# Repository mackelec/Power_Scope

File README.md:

# Power_Scope
Power Scope for $10

https://www.thebackshed.com/forum/forum_posts.asp?TID=11123&PN=1

Software is still a work in progress.

A minimal Oscilloscope design utilising a STM32F103 "Blue Pill" and a cheap mcuFriend 2.4" LCD, specifically to display the output voltage for an Inverter.  Along with displaying th eAc waveform it will display RMS voltage, Current and Power.

LCD library is compatible with the 8bit mcuFriend 2.4" and 3.5" LCD.

PCD features:

PCB is compatible with the 8 bit mcuFriend "UNO" lcds as well as the SPI based LCDs.

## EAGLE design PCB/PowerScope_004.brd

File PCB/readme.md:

"PowerScope_004_PCB_Order_20190317.zip"  contains the files sent for PCB manufacture.

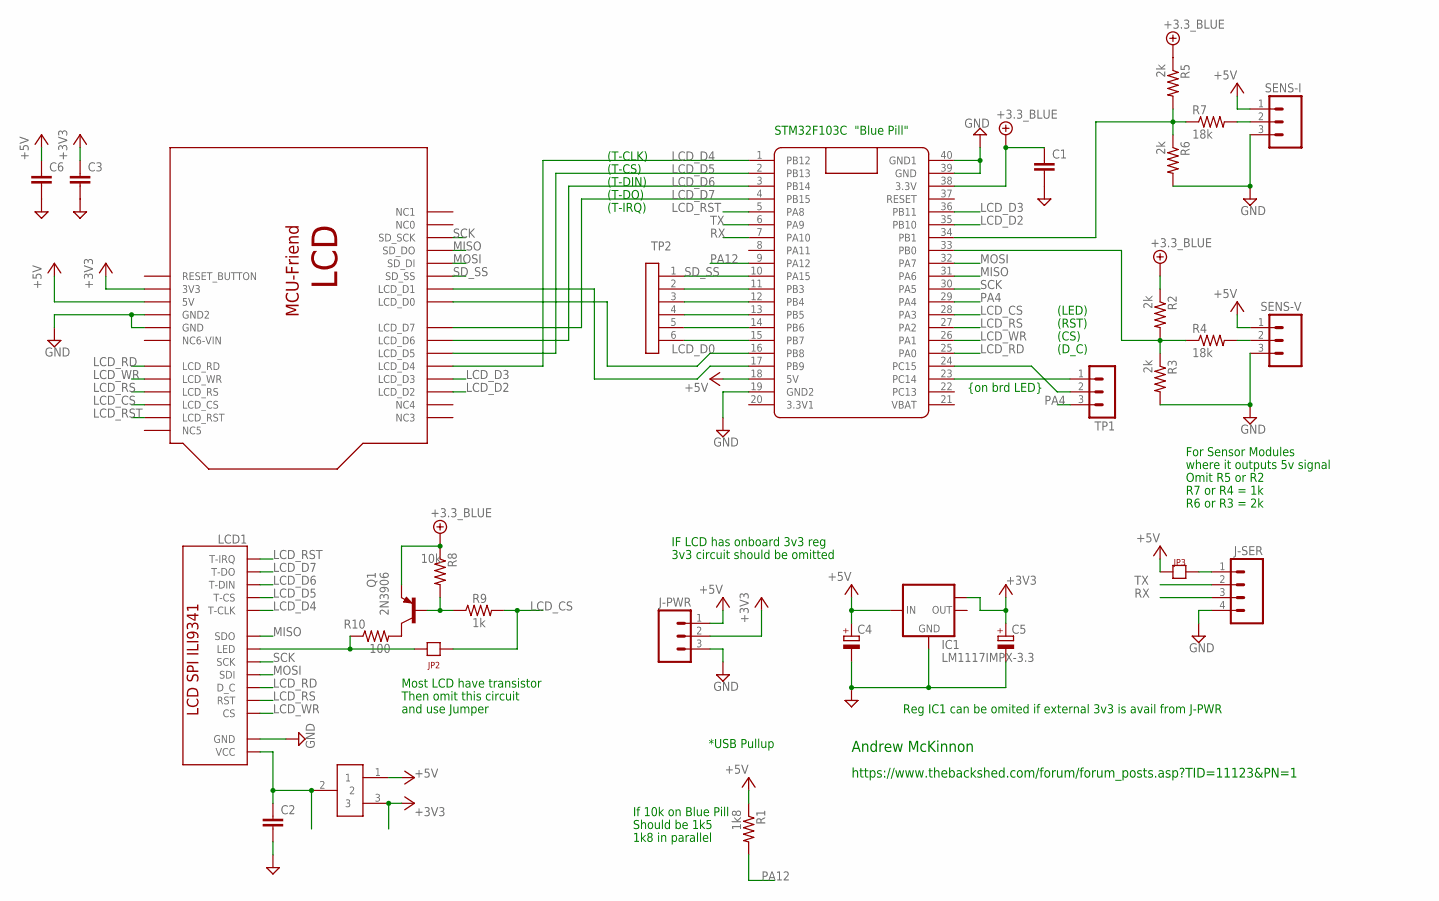
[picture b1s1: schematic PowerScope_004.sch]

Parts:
C1, C2, C3, C6: BCAP
C4, C5: C-RB200100; CPOL-RADIAL-10UF-25V
IC1: LM1117IMPX-3.3; SOT223
J-PWR: MO3POL; MOLEX-3
J-SER: MO4POL; MOLEX-4
JP1: JP1X3
JP2, JP3: JP1
LCD1: LCD_ILI9341_SPI_TREV; LCD_ILI9341_SPI_24T_REVERSE
Q1: 2N3906; TO92
R1: 1k8; R4_SP
R2, R3, R5, R6: 2k; R4_SP
R4, R7: 18k; R4_SP
R8: 10k; R4_SP
R9: 1k; R4_SP
R10: 100; R4_SP
SENS-I: MO3POL; MOLEX-3
SENS-V: MO3POL; MOLEX-3
TP1: MA03-1
TP2: SIL-6; SIL6
U$2: LCD_MCUFRIENDREV; LCD-MCUFRIEND-24T-REV
U$3: BLUE_PILL; BLUE_PILL_CLEAN

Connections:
+3V3: C3.1, C5.1 (+), IC1.TAB (OUT1), J-PWR.2, JP1.3, U$2.3V (3V3)
+5V: C4.1 (+), C6.1, IC1.3 (IN), J-PWR.1, JP1.1, JP3.1, R1.P$1 (1), SENS-I.1, SENS-V.1, U$2.5V, U$3.18 (5V)
+UB: C1.1, Q1.3 (E), R2.P$1 (1), R5.P$1 (1), R8.P$1 (1), U$3.38 (3.3V)
GND: C1.2, C2.2, C3.2, C4.2 (-), C5.2 (-), C6.2, IC1.1 (GND), J-PWR.3, J-SER.4, LCD1.GND, R3.P$2 (2), R6.P$2 (2), SENS-I.3, SENS-V.3, U$2.GND, U$2.GND2, U$3.19 (GND2), U$3.39 (GND), U$3.40 (GND1)
LCD_CS: JP2.2, R9.P$2 (2), U$2.LCD_CS, U$3.28 (PA3)
LCD_D0: U$2.LCD_D0, U$3.16 (PB8)
LCD_D2: U$2.LCD_D2, U$3.35 (PB10)
LCD_D3: U$2.LCD_D3, U$3.36 (PB11)
LCD_D4: LCD1.T_CLK (T-CLK), U$2.LCD_D4, U$3.1 (PB12)
LCD_D5: LCD1.T_CS (T-CS), U$2.LCD_D5, U$3.2 (PB13)
LCD_D6: LCD1.T_DI (T-DIN), U$2.LCD_D6, U$3.3 (PB14)
LCD_D7: LCD1.T_DO (T-DO), U$2.LCD_D7, U$3.4 (PB15)
LCD_RD: LCD1.D_C, U$2.LCD_RD, U$3.25 (PA0)
LCD_RS: LCD1.RST, U$2.LCD_RS, U$3.27 (PA2)
LCD_RST: LCD1.T-IRQ, U$2.LCD_RST, U$3.5 (PA8)
LCD_WR: LCD1.CS, U$2.LCD_WR, U$3.26 (PA1)
MISO: LCD1.SDO, U$2.SD_DO, U$3.31 (PA6)
MOSI: LCD1.SDI, U$2.SD_DI, U$3.32 (PA7)
unnamed: Q1.2 (B), R8.P$2 (2), R9.P$1 (1)
unnamed: U$2.LCD_D1, U$3.17 (PB9)
unnamed: Q1.1 (C), R10.P$2 (2)
unnamed: TP1.2, U$3.24 (PC15)
unnamed: TP2.6, U$3.15 (PB7)
unnamed: J-SER.1, JP3.2
unnamed: R4.P$2 (2), SENS-V.2
unnamed: R2.P$2 (2), R3.P$1 (1), R4.P$1 (1), U$3.33 (PB0)
unnamed: R7.P$2 (2), SENS-I.2
unnamed: R5.P$2 (2), R6.P$1 (1), R7.P$1 (1), U$3.34 (PB1)
unnamed: TP1.1, U$3.23 (PC14)
unnamed: TP2.5, U$3.14 (PB6)
unnamed: TP2.4, U$3.13 (PB5)
unnamed: TP2.3, U$3.12 (PB4)
unnamed: TP2.2, U$3.11 (PB3)
unnamed: JP2.1, LCD1.LED, R10.P$1 (1)
unnamed: C2.1, JP1.2, LCD1.VCC
PA4: TP1.3, U$3.29 (PA4)
PA12: R1.P$2 (2), U$3.9 (PA12)
RX: J-SER.3, U$3.7 (PA10)
SCK: LCD1.SCK, U$2.SD_SCK, U$3.30 (PA5)
SD_SS: TP2.1, U$2.SD_SS, U$3.10 (PA15)
TX: J-SER.2, U$3.6 (PA9)

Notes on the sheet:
*USB Pullup
If 10k on Blue Pill
Should be 1k5
1k8 in parallel
For Sensor Modules
where it outputs 5v signal
Omit R5 or R2
R7 or R4 = 1k
R6 or R3 = 2k
(RST)
(D_C)
(LED)
(CS)
(T-IRQ)
(T-DO)
(T-DIN)
(T-CS)
(T-CLK)
{on brd LED}
Most LCD have transistor
Then omit this circuit
and use Jumper
Reg IC1 can be omited if external 3v3 is avail from J-PWR
https://www.thebackshed.com/forum/forum_posts.asp?TID=11123&PN=1
Andrew McKinnon
IF LCD has onboard 3v3 reg
3v3 circuit should be omitted
STM32F103C "Blue Pill"

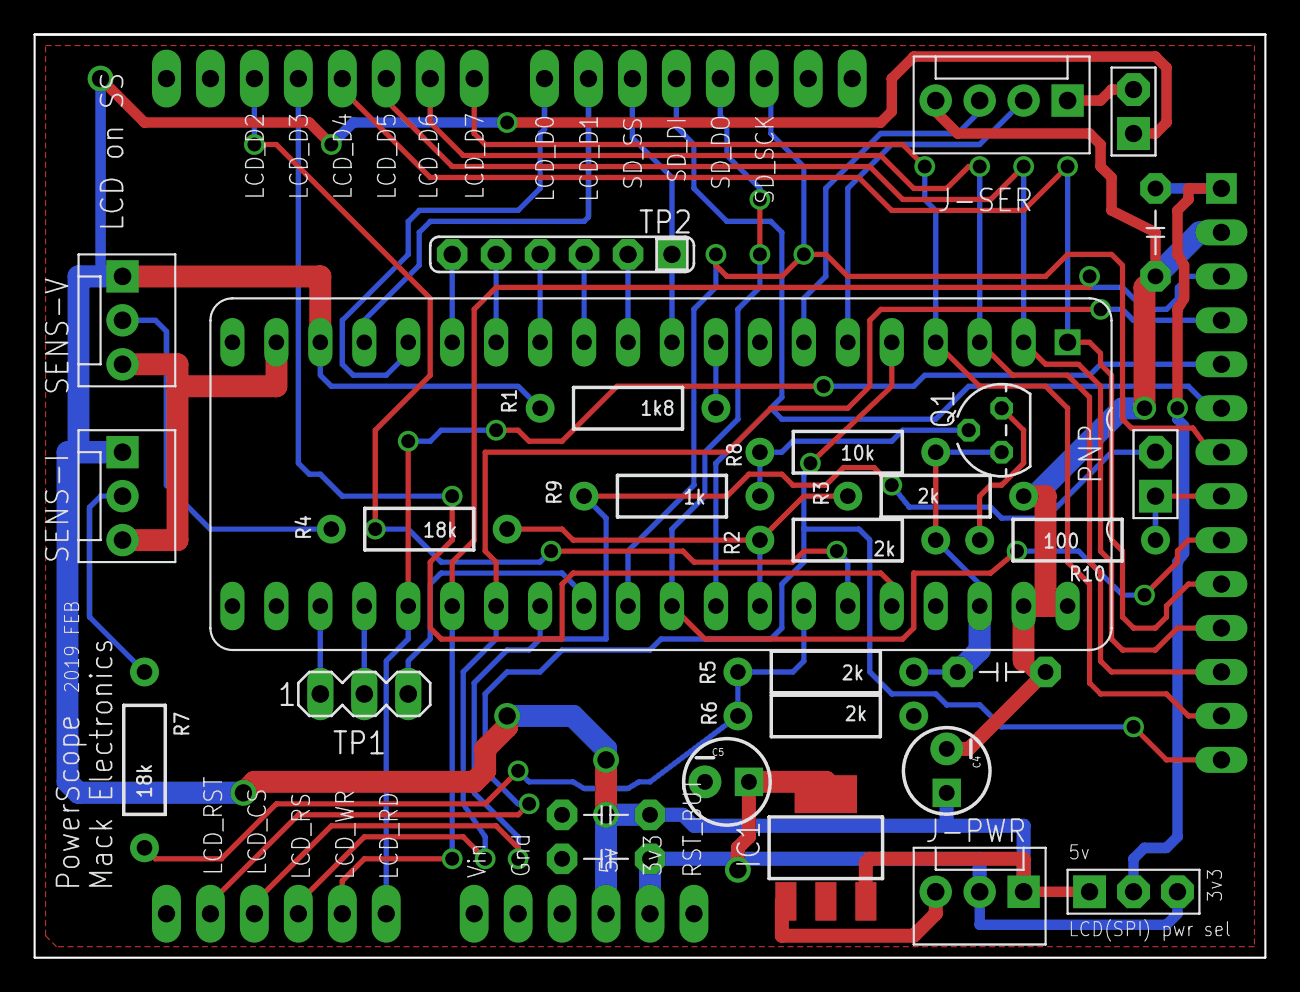
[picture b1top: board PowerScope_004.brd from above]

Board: 2 copper layers, 71.1 x 53.3 mm, 30 parts (0 on the bottom side), 41 nets.

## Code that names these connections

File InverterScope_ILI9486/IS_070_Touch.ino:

// These are the lcd pins used for touch 
#define LCD_RD PA0

#define LCD_RS PA2
#define LCD_CS PA3
#define LCD_D0 PB8
#define LCD_D1 PB9
#define LCD_D7 PB15
#define LCD_D6 PB14

#define LCD_RD PA0
#define LCD_WR PA1

#define YP LCD_WR  // must be an analog pin
#define XM LCD_RS  // must be an analog pin
#define YM LCD_D7   // can be a digital pin
#define XP LCD_D6   // can be a digital pin


TouchScreen ts = TouchScreen(XP, YP, XM, YM, 300);

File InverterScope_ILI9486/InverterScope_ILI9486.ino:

/*-------------------------------------------------------------------------------------------------------
 * 
 *   (c) Andrew McKinnon - 2019
 *    
 *    InverterScope - aka Power-Scope   released under the GNU GENERAL PUBLIC LICENSE Version 2, June 1991
 * 
 * 
 --------------------------------------------------------------------------------------------------------*/
#include <SPI.h>  
#include <STM32ADC.h>
#include <Streaming.h>
//#include <Adafruit_GFX.h>
#include "Adafruit_GFX.h"
#include <gfxfont.h>
#include <TouchScreen_STM.h>
//#include "Adafruit_ILI9341_8bit_STM.h" //modified lib for 8-bit parallel displays
#include <MCUFRIEND_kbv.h>

#define LCD_RD PA0
#define LCD_WR PA1
#define LCD_CD PA2
#define LCD_CS PA3
#define LCD_RESET PA8


HardwareTimer adcTimer(4);
STM32ADC adcV(ADC1);
STM32ADC adcI(ADC2);


/*----------------------------
 *    Size of LCD in Landscape
 -----------------------------*/
#define TFT_WIDTH  320
#define TFT_HEIGHT 240

/*----------------------------
 *    Size of Scope (graphing)
 *    -   Must be same / smaller
 *        than TFT_ parameters
 -----------------------------*/

#define FRAME_HEIGHT TFT_HEIGHT
#define FRAME_WIDTH TFT_WIDTH

/*----------------------------
 *  Frame_Period : 
 *  - time in microseconds
  ----------------------------*/

#define FRAME_PERIOD 50000

/*-----------------------------------------
 *    Persist, if True
 *    - last trace will not be erased on LCD
 -----------------------------------------*/
bool Persist = true;

#define testPin1 PA4
#define testPin2 PA5
#define testPin3 PA6

#define LED      PC13

uint8 adcPinV = PB0;
uint8 adcPinI = PB1;

bool testpinFlag;
//bool triggerMode = true;
volatile bool readyForTrigger = false;
volatile bool triggered = false;



volatile uint16 adcValueV=0;
volatile uint16 adcValueI=0;
volatile bool adcV_dataPresent;
volatile bool adcI_dataPresent;

uint16 adcPtr;
uint16 samplesA[FRAME_WIDTH];
uint16 samplesB[FRAME_WIDTH];
uint16 IsamplesA[FRAME_WIDTH];
uint16 IsamplesB[FRAME_WIDTH];
uint16 *samples;
uint16 *adcSamples;

uint16 zeroOffset = 0;
uint16 Vrms = 0;
uint16 Vrms_12bit = 0;
uint16 Vpp_12bit = 0;


uint16 Period_count = 0;   
uint32 Period_us = 0;          //  microseconds
uint16 Frequency = 0;


void setup() {
  //Serial.begin(115200);
  Serial.begin(250000);
  pinMode(testPin1,OUTPUT);
  pinMode(testPin2,OUTPUT);
  pinMode(testPin3,OUTPUT);
  pinMode(LED,OUTPUT);
  digitalWrite(LED,LOW);
  TFT_setup();
  samples = samplesA;
  adcSamples = samples;

  //*******  ADC setup

  adcV.calibrate();
  adcV.setSampleRate(ADC_SMPR_239_5);
  adcV.attachInterrupt(adcConvertedInt, ADC_EOC);
  adcV.setPins(&adcPinV, 1);

  adcI.calibrate();
  adcI.setSampleRate(ADC_SMPR_239_5);
  //adcI.attachInterrupt(int_ADCI,, ADC2_EOC);
  adcI.setPins(&adcPinI, 1);

    // -- sets up the adc control registers
    //    for Dual ADC, simultaneous sample
  ADC1->regs->CR1 |= 0x60000;
  ADC1->regs->CR2 |= 0x100;

  //*******  Timer setup  (156.25 microseconds, 6400Hz)
  //---
  //---  works out perfect for 50Hz
  //---  Frame = 50mS, 2.5 full cycles
  //---  Sample rate = 50ms / 320 (lcd width or frame)
  //---  equals 156.25 uSec - tada
  
  adcTimer.setMode(TIMER_CH4, TIMER_OUTPUT_COMPARE);
  adcTimer.pause();
  adcTimer.setPrescaleFactor(1);
  adcTimer.setCount(0);
  adcTimer.setOverflow(11250);
  adcTimer.setCompare(TIMER_CH4, 1);  
  adcTimer.attachCompare4Interrupt(timer_Handler);
  adcTimer.refresh();

  //********
  
  adcTimer.resume();
  //Serial << "TX buffer = " << SERIAL_TX_BUF_SIZE << endl;
  Serial << "Setup done" << endl;
  Serial.flush();
  digitalWrite(LED,HIGH);
}




void loop() 
{
 
}


void proc_Samples()
{
  if (adcPtr > 319 && adcPtr < 321)
  {
    gpio_write_bit(GPIOA, 6, HIGH);
    triggered = false;
    adcTimer.pause();
    adcPtr = 333;
    readyForTrigger = false;
    drawTrace();
    adcPtr = 0;
    readyForTrigger = true;
    gpio_write_bit(GPIOA, 6, LOW);
    adcTimer.resume();
  }
}

/*---------------------------------------------------------
 * 
 *    ADC callback routine
 *    -  Is called when conversion is finished
 * 
 ---------------------------------------------------------*/

void adcConvertedInt()
{
  static uint16 lastADC = 0;
  gpio_write_bit(GPIOA, 4, LOW);
  //-- read adc 32bit data register
  uint32 data = ADC1->regs->DR;
  adcValueV = data & 0xFFFF;
  adcValueI = data >> 16;

  //------------  If Frame full 
  
  if (adcPtr > 319) 
  {
    if (triggered)
    {
      //gpio_write_bit(GPIOA, 5, LOW);
      if (adcSamples == samplesA)
      {
        samples = samplesA;
        adcSamples = samplesB;
      }
      else
      {
        samples = samplesB;
        adcSamples = samplesA;
      }
      proc_Samples();
    }
    triggered = false;
    
    lastADC = 0;
    return;
  }

  //------------  Saving Frame data
  
  if (triggered)
  {
    //gpio_write_bit(GPIOA, 5, HIGH);
    adcSamples[adcPtr] = adcValueV;
    adcPtr ++;
  }

  //------------  Looking for Trigger
  
  else
  {
    if (lastADC == 0) 
    {
      lastADC = adcValueV;
      return;
    }

    int y1 = (int) (adcValueV - 2048);
    int y2 = (int) (lastADC - 2048);
//    y1 -= (int) zeroOffset;
//    y2 -= (int) zeroOffset;
    lastADC = adcValueV;
    if (y2 < 0 && y1 >= 0)
    {
      triggered = true;
    }
  }
}

/*------------------------------------------------------------
 *    Timer handler - fires every 156.25uSec
 *    -   Starts ADC conversion.
 *        Only needs to Start ADC1 conversion.
 *        As Dual mode is set, ADC2 conversion is started by ADC1.
 *    -   Sets testPin1 HIGH, 
 *        testPin1 is cleared LOW when the ADC callBack Occurs.   
 *        Use a Scope to check timing is good and no over-runs
 -------------------------------------------------------------*/

void timer_Handler()
{
  //----  turn testPin1 high
  gpio_write_bit(GPIOA, 4, HIGH);
  adcV.startConversion();
}

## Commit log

2019-03-13 Create junk
